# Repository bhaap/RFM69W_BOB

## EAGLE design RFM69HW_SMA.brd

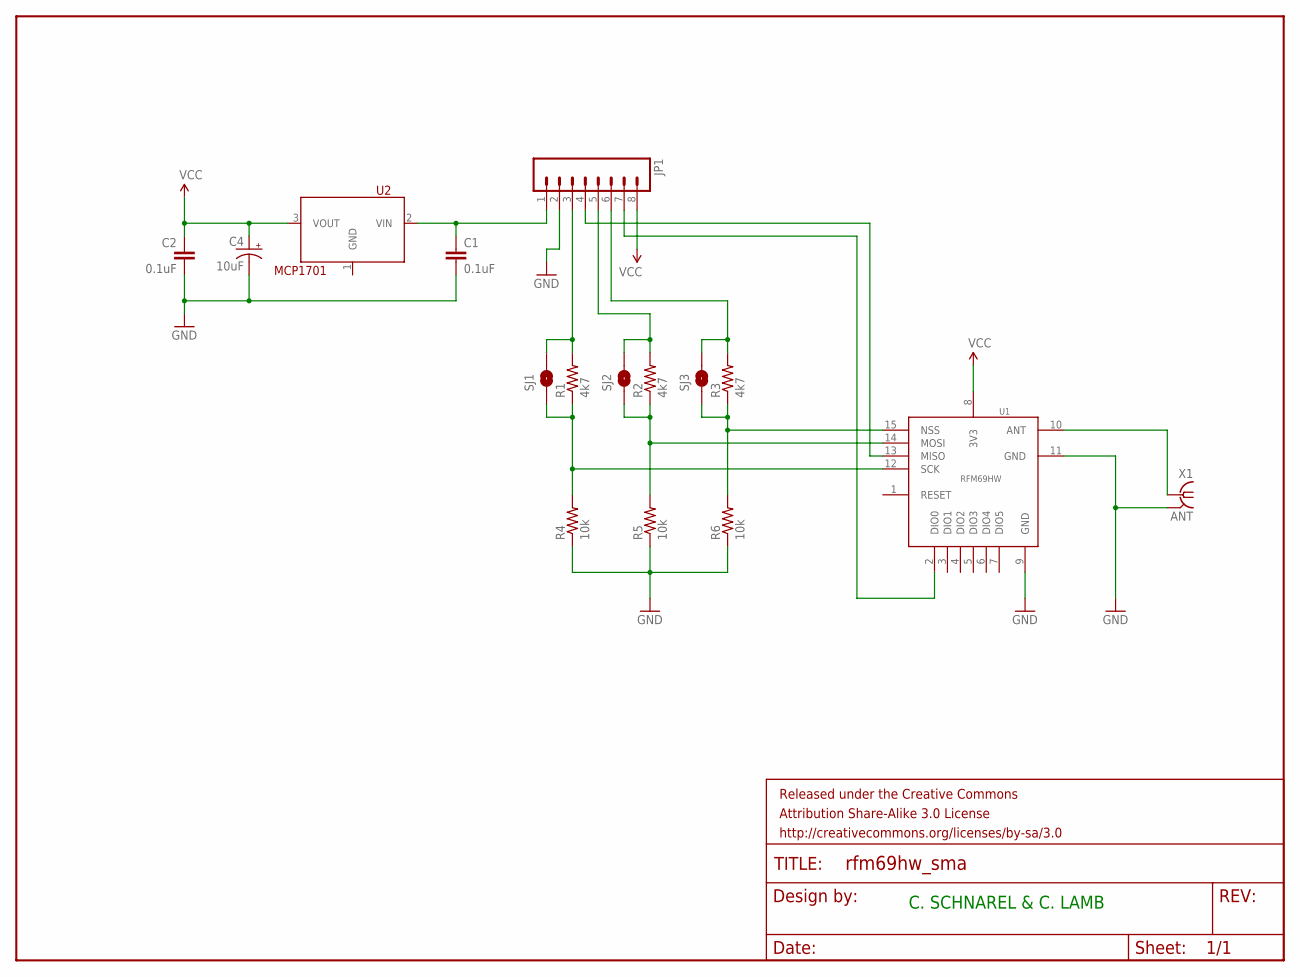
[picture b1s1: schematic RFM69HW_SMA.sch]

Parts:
C1, C2: 0.1uF; 0805
C4: 10uF; 0805-POL
FRAME1: FRAME-LETTER; CREATIVE_COMMONS
JP1: M08LONGPADS; 1X08_LONGPADS
R1, R2, R3: 4k7; 0805
R4, R5, R6: 10k; 0805
SJ1, SJ2, SJ3: SOLDERJUMPERNO; SJ_2S-NO
U1: RFM69HW; RFM69
U2: MCP1701; SOT-89
X1: ANT; TE-SMA-JACK-STR

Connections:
GND: C1.2, C2.2, C4.2 (-), JP1.2, R4.1, R5.1, R6.1, U1.9 (GND), U1.11 (GND), X1.2, X1.3 (2), X1.4 (2), X1.5 (2)
unnamed: R3.1, R6.2, SJ3.1, U1.15 (NSS)
unnamed: C1.1, JP1.1, U2.2 (VIN)
unnamed: JP1.4, U1.13 (MISO)
unnamed: JP1.7, U1.2 (DIO0)
unnamed: R2.1, R5.2, SJ2.1, U1.14 (MOSI)
unnamed: JP1.3, R1.2, SJ1.2
unnamed: JP1.5, R2.2, SJ2.2
unnamed: JP1.6, R3.2, SJ3.2
unnamed: R1.1, R4.2, SJ1.1, U1.12 (SCK)
unnamed: U1.10 (ANT), X1.1
VCC: C2.1, C4.1 (+), JP1.8, U1.8 (3V3), U2.3 (VOUT)

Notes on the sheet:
C. SCHNAREL & C. LAMB

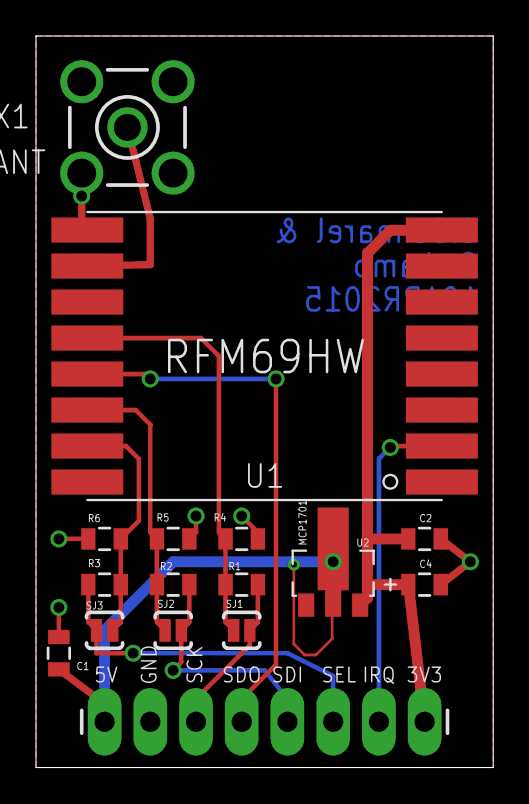
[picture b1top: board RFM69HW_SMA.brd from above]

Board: 2 copper layers, 25.4 x 40.6 mm, 17 parts (0 on the bottom side), 12 nets.

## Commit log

2015-04-11 New SMA break out board
    Eagle Board and schematic for a variant that has room for an SMA
    connector and the IO pins broken out
2015-04-11 Slight relayout
    Re-layout. Break out all I/O pins. Use RFM69HW variant (same pinout).
2016-10-31 Update to remove JP2 and JP3

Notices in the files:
parts and their libraries:
SparkFun-Aesthetics: Licensing: CC v3.0 Share-Alike You are welcome to use this library for commercial purposes.
SparkFun-Aesthetics: Released under the Creative Commons Attribution Share-Alike 3.0 License
SparkFun-Aesthetics: http://creativecommons.org/licenses/by-sa/3.0
